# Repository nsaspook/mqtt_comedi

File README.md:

C programs for interfacing a Comedi DAQ board to MQTT using jSON data format

For bmc Q84 board firmware and hardware files use branch: opifixes

For bmc Linux control for Orange Pi use branch: opifixes

For bmc Linux control for Rasperry Pi use branch: fixes64

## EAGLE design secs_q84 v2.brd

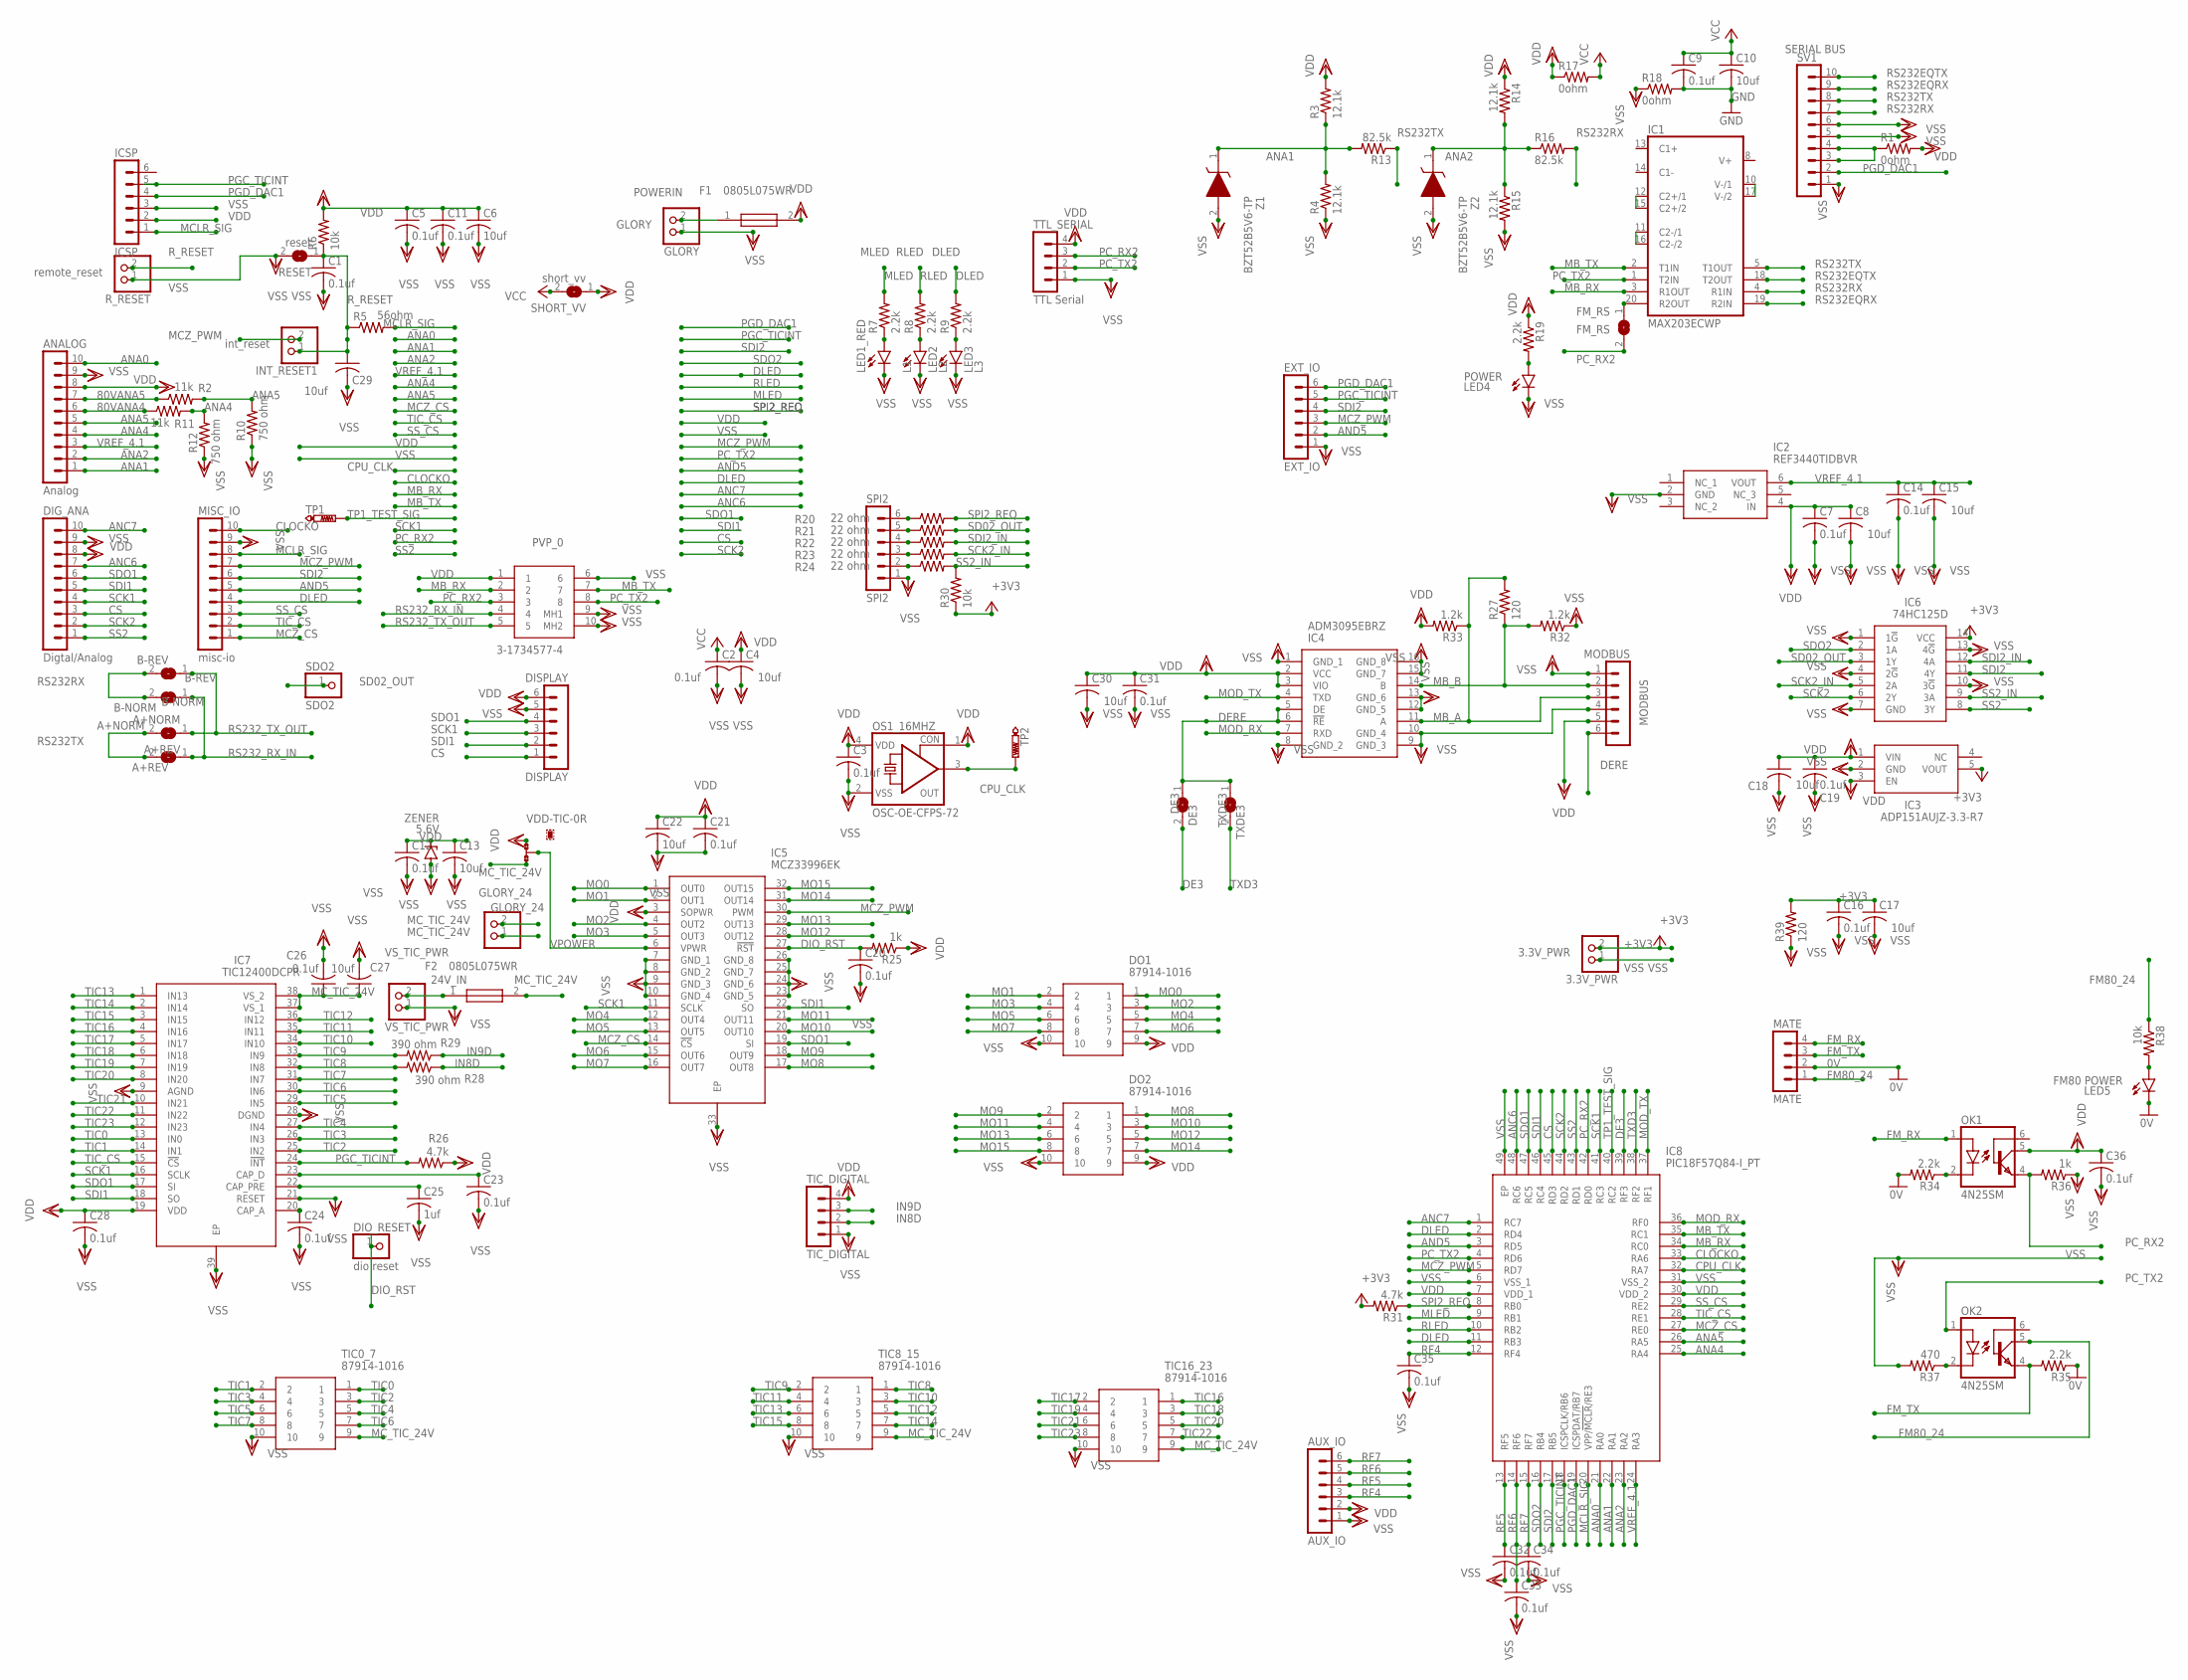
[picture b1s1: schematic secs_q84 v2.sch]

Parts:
3.3V_PWR: 3.3V_PWR; 1X02
A+NORM: A+NORM; SJ
A+REV: A+REV; SJ
ANALOG: Analog; MA10-1
AUX_IO: AUX_IO; MA06-1
B-NORM: B-NORM; SJ
B-REV: B-REV; SJ
C1, C2, C3, C5, C7, C9, C11, C12, C14, C16, C19, C20, C21, C23, C24, C26, C28, C31: 0.1uf; C0805
C4, C6, C8, C10, C13, C15, C17, C18, C22, C27, C29, C30: 10uf; C0805
C25: 1uf; C0805
C32, C33, C34, C35, C36: 0.1uf; C0603
DE3: DE3; SJ
DIG_ANA: Digtal/Analog; MA10-1
DIO_RESET: dio reset; 1X01
DISPLAY: DISPLAY; MA06-1
DO1, DO2: 87914-1016; 879141016
EXT_IO: EXT_IO; MA06-1
F1, F2: 0805L075WR; FUSC2114X125N
FM_RS: FM_RS; SJ
GLORY: GLORY; 1X02
GLORY_24: GLORY_24; 1X02
IC1: MAX203ECWP; SO20L
IC2: REF3440TIDBVR; SOT95P280X145-6N
IC3: ADP151AUJZ-3.3-R7; SOT95P280X100-5N
IC4: ADM3095EBRZ; SOIC127P600X175-16N
IC5: MCZ33996EK; SOP65P1030X265-33N
IC6: 74HC125D; SOIC127P600X175-14N
IC7: TIC12400DCPR; SOP50P640X120-39N
IC8: PIC18F57Q84-I_PT; QFP50P900X900X120-49N
ICSP: ICSP; MA06-1
INT_RESET1: int_reset; 1X02
LED1_RED: L1; CHIPLED_0805
LED2: L2; CHIPLED_0805
LED3: L3; CHIPLED_0805
LED4: POWER; CHIP-LED0603
LED5: FM80 POWER; CHIP-LED0603
MATE: MATE; MA04-1
MISC_IO: misc-io; MA10-1
MODBUS: MODBUS; MA06-1
OK1, OK2: 4N25SM; DIL6-SMD
OS1_16MHZ: OSC-OE-CFPS-72; 7.2X5.2-4-PAD
PVP_0: 3-1734577-4; 317345774
R1, R17, R18: 0ohm; R0805
R2, R11: 11k; M1206
R3, R4, R14, R15: 12.1k; R0805
R5: 56ohm; R0805
R6, R30, R38: 10k; R0805
R7, R8, R9, R19, R34, R35: 2.2k; R0805
R10, R12: 750 ohm; M1206
R13, R16: 82.5k; R0805
R20, R21, R22, R23, R24: 22 ohm; R0805
R25, R36: 1k; R0805
R26, R31: 4.7k; R0805
R27, R39: 120; R0805
R28, R29: 390 ohm; R0805
R32, R33: 1.2k; R0805
R37: 470; R0805
RESET: reset; SJ
R_RESET: remote_reset; 1X02
SDO2: SDO2; 1X01
SHORT_VV: short_vv; SJ
SPI2: SPI2; MA06-1
SV1: SERIAL BUS; MA10-1
TIC0_7, TIC8_15, TIC16_23: 87914-1016; 879141016
TIC_DIGITAL: TIC_DIGITAL; MA04-1
TP1, TP2: PTR1PAD1-13; P1-13
TTL_SERIAL: TTL Serial; MA04-1
TXDE3: TXDE3; SJ
VDD-TIC: 0R-JUMPA; A0R-JMP
VS_TIC_PWR: VS_TIC_PWR; 1X02
Z1, Z2: BZT52B5V6-TP; SOD3716X135N
ZENER: 5.6V; SMB

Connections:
0V: LED5.C, MATE.2, R34.2, R35.1
24V_IN: F2.1, VS_TIC_PWR.2
80VANA4: ANALOG.6, R11.1
80VANA5: ANALOG.7, R2.1
+3V3: 3.3V_PWR.2, C16.1, C17.1, IC3.5 (VOUT), IC6.14 (VCC), R30.1, R31.2, R39.2
ANA0: ANALOG.10, IC8.21 (RA0)
ANA1: ANALOG.1, IC8.22 (RA1), R3.1, R4.2, R13.2, Z1.1 (K)
ANA2: ANALOG.2, IC8.23 (RA2), R14.2, R15.1, R16.1, Z2.1 (K)
ANA4: ANALOG.4, IC8.25 (RA4), R11.2, R12.2
ANA5: ANALOG.5, IC8.26 (RA5), R2.2, R10.2
ANC6: DIG_ANA.7, IC8.48 (RC6)
ANC7: DIG_ANA.10, IC8.1 (RC7)
AND5: EXT_IO.2, IC8.3 (RD5), MISC_IO.5
CLOCKO: IC8.33 (RA6), MISC_IO.10
CPU_CLK: IC8.32 (RA7), OS1_16MHZ.3 (OUT), TP2.TP
CS: DIG_ANA.3, DISPLAY.1, IC8.45 (RD3)
DE3: DE3.2, IC8.39 (RF3)
DERE: DE3.1, IC4.5 (DE), IC4.6 (!RE), MODBUS.6, TXDE3.1
DIO_RST: C20.1, DIO_RESET.1, IC5.27 (!RST), R25.2
DLED: IC8.2 (RD4), IC8.11 (RB3), MISC_IO.4, R9.2
DPOWER: R1.1, SV1.3, SV1.4
FM80_24: MATE.1, OK2.5 (COL), R38.1
FM_RX: MATE.4, OK1.1 (A)
FM_TX: MATE.3, OK2.4 (EMI), R35.2
GND: C9.2, C10.2, IC1.6 (GND), IC1.9 (GND), R18.2
IN8D: R28.1, TIC_DIGITAL.2
IN9D: R29.1, TIC_DIGITAL.3
MB_A: IC4.11 (A), MODBUS.3, R27.2, R33.1
MB_B: IC4.14 (B), MODBUS.2, R27.1, R32.2
MB_RX: IC1.3 (R1OUT), IC8.34 (RC0), PVP_0.2
MB_TX: IC1.2 (T1IN), IC8.35 (RC1), PVP_0.7
MCLR_SIG: IC8.20 (VPP/!MCLR!/RE3), ICSP.1, MISC_IO.8, R5.2
MCZ_CS: IC5.14 (!CS), IC8.27 (RE0), MISC_IO.1
MCZ_PWM: EXT_IO.3, IC5.30 (PWM), IC8.5 (RD7), INT_RESET1.2, MISC_IO.7
MC_TIC_24V: C26.1, C27.1, F2.2, GLORY_24.1, GLORY_24.2, IC7.37 (VS_1), IC7.38 (VS_2), TIC0_7.9, TIC8_15.9, TIC16_23.9, VDD-TIC.3
MLED: IC8.9 (RB1), R7.2
MO0: DO1.1, IC5.1 (OUT0)
MO1: DO1.2, IC5.2 (OUT1)
MO2: DO1.3, IC5.4 (OUT2)
MO3: DO1.4, IC5.5 (OUT3)
MO4: DO1.5, IC5.12 (OUT4)
MO5: DO1.6, IC5.13 (OUT5)
MO6: DO1.7, IC5.15 (OUT6)
MO7: DO1.8, IC5.16 (OUT7)
MO8: DO2.1, IC5.17 (OUT8)
MO9: DO2.2, IC5.18 (OUT9)
MO10: DO2.3, IC5.20 (OUT10)
MO11: DO2.4, IC5.21 (OUT11)
MO12: DO2.5, IC5.28 (OUT12)
MO13: DO2.6, IC5.29 (OUT13)
MO14: DO2.7, IC5.31 (OUT14)
MO15: DO2.8, IC5.32 (OUT15)
MOD_RX: IC4.7 (RXD), IC8.36 (RF0)
MOD_TX: IC4.4 (TXD), IC8.37 (RF1)
unnamed: IC1.10 (V-/1), IC1.17 (V-/2)
unnamed: IC1.12 (C2+/1), IC1.15 (C2+/2)
unnamed: LED4.A, R19.2
unnamed: LED1_RED.A, R7.1
unnamed: LED2.A, R8.1
unnamed: LED3.A, R9.1
unnamed: IC1.11 (C2-/1), IC1.16 (C2-/2)
unnamed: R20.1, SPI2.6
unnamed: R21.1, SPI2.5
unnamed: R22.1, SPI2.4
unnamed: R23.1, SPI2.3
unnamed: R24.1, SPI2.2
unnamed: FM_RS.1, IC1.20 (R2OUT)
unnamed: OK1.2 (C), R34.1
unnamed: LED5.A, R38.2
unnamed: OK2.2 (C), R37.1
unnamed: C23.1, IC7.23 (CAP_D)
unnamed: C25.1, IC7.22 (CAP_PRE)
unnamed: C24.1, IC7.20 (CAP_A)
PC_RX2: FM_RS.2, IC8.42 (RD0), OK1.4 (EMI), PVP_0.3, R36.2, TTL_SERIAL.3
PC_TX2: IC1.1 (T2IN), IC8.4 (RD6), OK2.1 (A), PVP_0.8, TTL_SERIAL.2
PGC_TICINT: EXT_IO.5, IC7.24 (!INT), IC8.18 (ICSPCLK/RB6), ICSP.5, R26.2
PGD_DAC1: EXT_IO.6, IC8.19 (ICSPDAT/RB7), ICSP.4, SV1.2
POWERIN: F1.1, GLORY.2
RF4: AUX_IO.3, C35.1, IC8.12 (RF4)
RF5: AUX_IO.4, C32.1, IC8.13 (RF5)
RF6: AUX_IO.5, C33.1, IC8.14 (RF6)
RF7: AUX_IO.6, C34.1, IC8.15 (RF7)
RLED: IC8.10 (RB2), R8.2
RS232EQRX: IC1.19 (R2IN), SV1.9
RS232EQTX: IC1.18 (T2OUT), SV1.10
RS232RX: B-NORM.2, B-REV.2, IC1.4 (R1IN), R16.2, SV1.7
RS232TX: A+NORM.2, A+REV.2, IC1.5 (T1OUT), R13.1, SV1.8
RS232_RX_IN: A+REV.1, B-NORM.1, PVP_0.4
RS232_TX_OUT: A+NORM.1, B-REV.1, PVP_0.5
R_RESET: C1.1, C29.1, INT_RESET1.1, R5.1, R6.1, RESET.1, R_RESET.2
SCK1: DIG_ANA.4, DISPLAY.3, IC5.11 (SCLK), IC7.16 (SCLK), IC8.41 (RC3)
SCK2: DIG_ANA.2, IC6.6 (2Y), IC8.44 (RD2)
SCK2_IN: IC6.5 (2A), R23.2
SD02_OUT: IC6.3 (1Y), R21.2, SDO2.1
SDI1: DIG_ANA.5, DISPLAY.2, IC5.22 (SO), IC7.18 (SO), IC8.46 (RC4)
SDI2: EXT_IO.4, IC6.11 (4Y), IC8.17 (RB5), MISC_IO.6
SDI2_IN: IC6.12 (4A), R22.2
SDO1: DIG_ANA.6, DISPLAY.4, IC5.19 (SI), IC7.17 (SI), IC8.47 (RC5)
SDO2: IC6.2 (1A), IC8.16 (RB4)
SPI2_REQ: IC8.8 (RB0), R20.2, R31.1
SS2: DIG_ANA.1, IC6.8 (3Y), IC8.43 (RD1)
SS2_IN: IC6.9 (3A), R24.2, R30.2
SS_CS: IC8.29 (RE2), MISC_IO.3
TIC0: IC7.13 (IN0), TIC0_7.1
TIC1: IC7.14 (IN1), TIC0_7.2
TIC2: IC7.25 (IN2), TIC0_7.3
TIC3: IC7.26 (IN3), TIC0_7.4
TIC4: IC7.27 (IN4), TIC0_7.5
TIC5: IC7.29 (IN5), TIC0_7.6
TIC6: IC7.30 (IN6), TIC0_7.7
TIC7: IC7.31 (IN7), TIC0_7.8
TIC8: IC7.32 (IN8), R28.2, TIC8_15.1
TIC9: IC7.33 (IN9), R29.2, TIC8_15.2
TIC10: IC7.34 (IN10), TIC8_15.3
TIC11: IC7.35 (IN11), TIC8_15.4
TIC12: IC7.36 (IN12), TIC8_15.5
TIC13: IC7.1 (IN13), TIC8_15.6
TIC14: IC7.2 (IN14), TIC8_15.7
TIC15: IC7.3 (IN15), TIC8_15.8
TIC16: IC7.4 (IN16), TIC16_23.1
TIC17: IC7.5 (IN17), TIC16_23.2
TIC18: IC7.6 (IN18), TIC16_23.3
TIC19: IC7.7 (IN19), TIC16_23.4
TIC20: IC7.8 (IN20), TIC16_23.5
TIC21: IC7.10 (IN21), TIC16_23.6
TIC22: IC7.11 (IN22), TIC16_23.7
TIC23: IC7.12 (IN23), TIC16_23.8
TIC_CS: IC7.15 (!CS), IC8.28 (RE1), MISC_IO.2
TP1_TEST_SIG: IC8.40 (RC2), TP1.TP
TXD3: IC8.38 (RF2), TXDE3.2
VCC: C2.1, C9.1, C10.1, IC1.7 (VCC), R17.2, SHORT_VV.2
VDD: ANALOG.8, AUX_IO.2, C3.1, C4.1, C5.1, C6.1, C7.1, C8.1, C11.1, C12.1, C13.1, C18.1, C19.1, C21.1, C22.1, C28.1, C30.1, C31.1, C36.1, DIG_ANA.8, DISPLAY.6, DO1.9, DO2.9, F1.2, IC2.4 (IN), IC3.1 (VIN), IC3.3 (EN), IC4.2 (VCC), IC4.3 (VIO), IC5.3 (SOPWR), IC7.19 (VDD), IC8.7 (VDD_1), IC8.30 (VDD_2), ICSP.2, MODBUS.5, OK1.5 (COL), OS1_16MHZ.1 (CON), OS1_16MHZ.4 (VDD), PVP_0.1, R1.2, R3.2, R6.2, R14.1, R17.1, R19.1, R25.1, R26.1, R33.2, SHORT_VV.1, TIC_DIGITAL.4, TTL_SERIAL.4, VDD-TIC.1, ZENER.C
VPOWER: IC5.6 (VPWR), VDD-TIC.2
VREF_4.1: ANALOG.3, C14.1, C15.1, IC2.6 (VOUT), IC8.24 (RA3)
VSS: 3.3V_PWR.1, ANALOG.9, AUX_IO.1, C1.2, C2.2, C3.2, C4.2, C5.2, C6.2, C7.2, C8.2, C11.2, C12.2, C13.2, C14.2, C15.2, C16.2, C17.2, C18.2, C19.2, C20.2, C21.2, C22.2, C23.2, C24.2, C25.2, C26.2, C27.2, C28.2, C29.2, C30.2, C31.2, C32.2, C33.2, C34.2, C35.2, C36.2, DIG_ANA.9, DISPLAY.5, DO1.10, DO2.10, EXT_IO.1, GLORY.1, IC2.2 (GND), IC3.2 (GND), IC4.1 (GND_1), IC4.8 (GND_2), IC4.9 (GND_3), IC4.10 (GND_4), IC4.12 (GND_5), IC4.13 (GND_6), IC4.15 (GND_7), IC4.16 (GND_8), IC5.7 (GND_1), IC5.8 (GND_2), IC5.9 (GND_3), IC5.10 (GND_4), IC5.23 (GND_5), IC5.24 (GND_6), IC5.25 (GND_7), IC5.26 (GND_8), IC5.33 (EP), IC6.1 (1!G), IC6.4 (2!G), IC6.7 (GND), IC6.10 (3!G), IC6.13 (4!G), IC7.9 (AGND), IC7.21 (RESET), IC7.28 (DGND), IC7.39 (EP), IC8.6 (VSS_1), IC8.31 (VSS_2), IC8.49 (EP), ICSP.3, LED1_RED.C, LED2.C, LED3.C, LED4.C, MISC_IO.9, MODBUS.1, MODBUS.4, OS1_16MHZ.2 (VSS), PVP_0.6, PVP_0.9 (MH1), PVP_0.10 (MH2), R4.1, R10.1, R12.1, R15.2, R18.1, R32.1, R36.1, R37.2, R39.1, RESET.2, R_RESET.1, SPI2.1, SV1.1, SV1.5, SV1.6, TIC0_7.10, TIC8_15.10, TIC16_23.10, TIC_DIGITAL.1, TTL_SERIAL.1, VS_TIC_PWR.1, Z1.2 (A), Z2.2 (A), ZENER.A

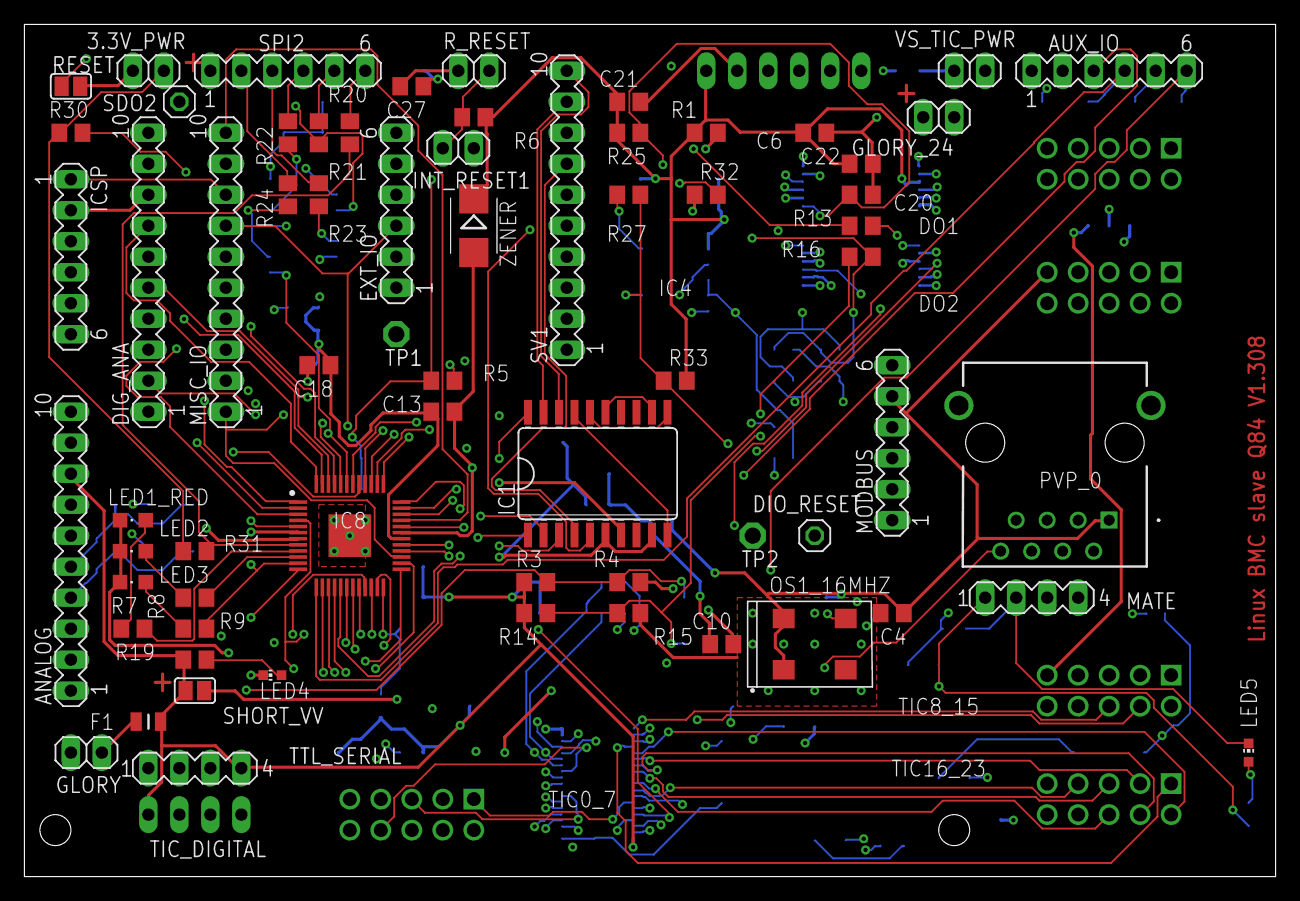
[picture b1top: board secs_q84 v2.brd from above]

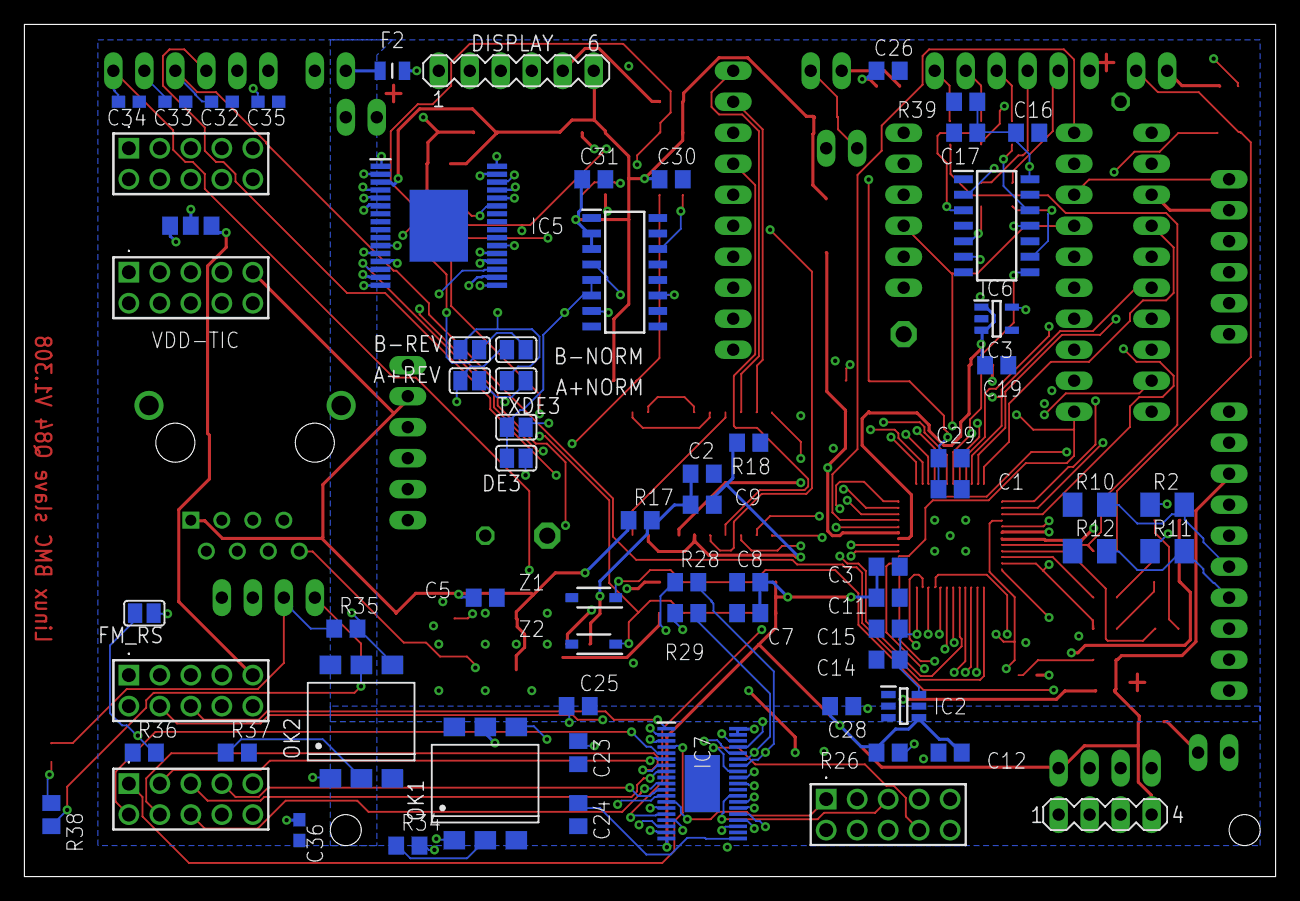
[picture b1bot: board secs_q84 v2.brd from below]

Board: 4 copper layers, 102.5 x 69.8 mm, 135 parts (68 on the bottom side), 135 nets.

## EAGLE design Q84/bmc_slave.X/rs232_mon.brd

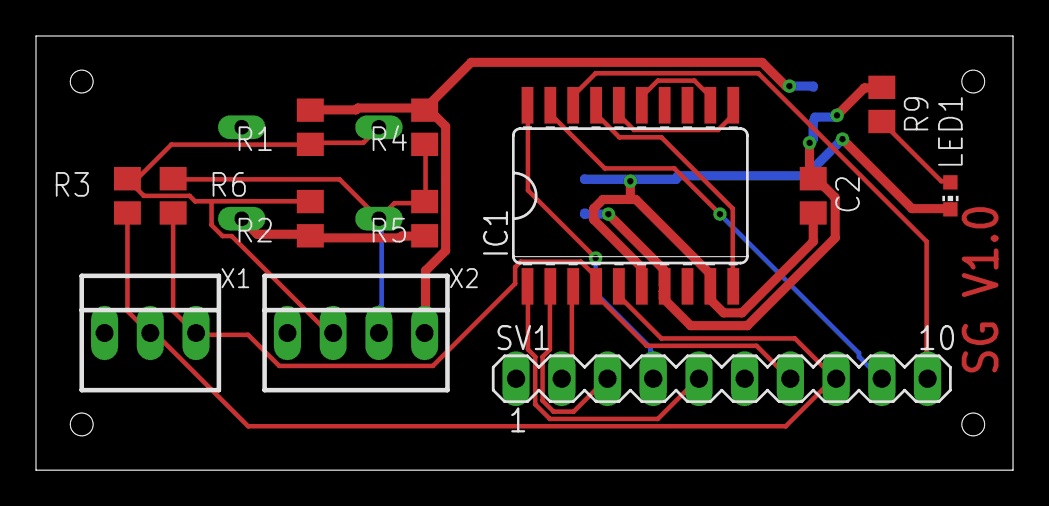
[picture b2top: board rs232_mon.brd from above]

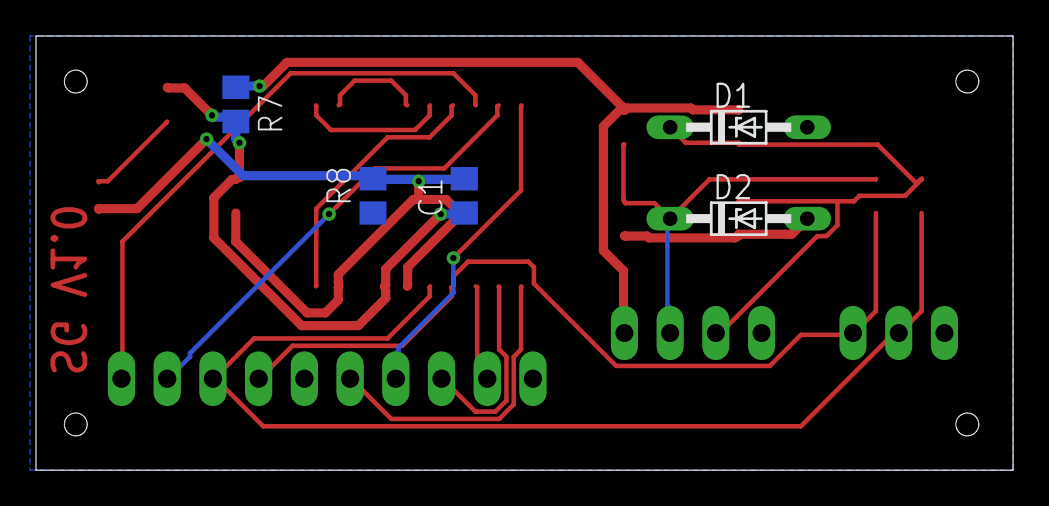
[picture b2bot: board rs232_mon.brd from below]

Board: 2 copper layers, 54.3 x 24.1 mm, 18 parts (5 on the bottom side), 18 nets.

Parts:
C1: 0.1uf; C0805
C2: 10uf; C0805
D1, D2: 5.6V; DO34Z7
IC1: MAX203ECWP; SO20L
LED1: POWER; CHIP-LED0603
R1, R2, R4, R5: 12.1k; R0805
R3, R6: 86.6k; R0805
R7, R8: 0ohm; R0805
R9: 1k; R0805
SV1: SERIAL BUS; MA10-1
X1: RS232 LINES; 22-23-2031
X2: ADC POWER; 22-23-2041

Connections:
EQRX: IC1.20, SV1.4
EQTX: IC1.1, SV1.5
GND: C1.2, C2.2, IC1.6, IC1.9, LED1.C, R8.2
MCURX: IC1.3, SV1.2
MCUTX: IC1.2, SV1.3
unnamed: D1.C, R1.1, R2.2, R3.2, X2.2
unnamed: D2.C, R4.2, R5.1, R6.1, X2.3
unnamed: LED1.A, R9.2
unnamed: IC1.10, IC1.17
unnamed: IC1.11, IC1.16
unnamed: IC1.12, IC1.15
RS232EQRX: IC1.19, SV1.9
RS232EQTX: IC1.18, SV1.10
RS232RX: IC1.4, R6.2, SV1.7, X1.3
RS232TX: IC1.5, R3.1, SV1.8, X1.2
VCC: C1.1, C2.1, IC1.7, R7.2, R9.1
VDD: R1.2, R4.1, R7.1, X2.4
VSS: D1.A, D2.A, R2.1, R5.2, R8.1, SV1.1, SV1.6, X1.1, X2.1

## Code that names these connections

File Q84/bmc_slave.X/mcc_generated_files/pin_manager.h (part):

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// get/set channel_ANA0 aliases
#define channel_ANA0_TRIS                 TRISAbits.TRISA0
#define channel_ANA0_LAT                  LATAbits.LATA0
#define channel_ANA0_PORT                 PORTAbits.RA0
#define channel_ANA0_WPU                  WPUAbits.WPUA0
#define channel_ANA0_OD                   ODCONAbits.ODCA0
#define channel_ANA0_ANS                  ANSELAbits.ANSELA0
#define channel_ANA0_SetHigh()            do { LATAbits.LATA0 = 1; } while(0)
#define channel_ANA0_SetLow()             do { LATAbits.LATA0 = 0; } while(0)
#define channel_ANA0_Toggle()             do { LATAbits.LATA0 = ~LATAbits.LATA0; } while(0)
#define channel_ANA0_GetValue()           PORTAbits.RA0
#define channel_ANA0_SetDigitalInput()    do { TRISAbits.TRISA0 = 1; } while(0)
#define channel_ANA0_SetDigitalOutput()   do { TRISAbits.TRISA0 = 0; } while(0)
#define channel_ANA0_SetPullup()          do { WPUAbits.WPUA0 = 1; } while(0)
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// get/set channel_ANA1 aliases
#define channel_ANA1_TRIS                 TRISAbits.TRISA1
#define channel_ANA1_LAT                  LATAbits.LATA1
#define channel_ANA1_PORT                 PORTAbits.RA1
#define channel_ANA1_WPU                  WPUAbits.WPUA1
#define channel_ANA1_OD                   ODCONAbits.ODCA1
#define channel_ANA1_ANS                  ANSELAbits.ANSELA1
#define channel_ANA1_SetHigh()            do { LATAbits.LATA1 = 1; } while(0)
#define channel_ANA1_SetLow()             do { LATAbits.LATA1 = 0; } while(0)
#define channel_ANA1_Toggle()             do { LATAbits.LATA1 = ~LATAbits.LATA1; } while(0)
#define channel_ANA1_GetValue()           PORTAbits.RA1
#define channel_ANA1_SetDigitalInput()    do { TRISAbits.TRISA1 = 1; } while(0)
#define channel_ANA1_SetDigitalOutput()   do { TRISAbits.TRISA1 = 0; } while(0)
#define channel_ANA1_SetPullup()          do { WPUAbits.WPUA1 = 1; } while(0)
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// get/set channel_ANA2 aliases
#define channel_ANA2_TRIS                 TRISAbits.TRISA2
#define channel_ANA2_LAT                  LATAbits.LATA2
#define channel_ANA2_PORT                 PORTAbits.RA2
#define channel_ANA2_WPU                  WPUAbits.WPUA2
#define channel_ANA2_OD                   ODCONAbits.ODCA2
#define channel_ANA2_ANS                  ANSELAbits.ANSELA2
#define channel_ANA2_SetHigh()            do { LATAbits.LATA2 = 1; } while(0)
#define channel_ANA2_SetLow()             do { LATAbits.LATA2 = 0; } while(0)
#define channel_ANA2_Toggle()             do { LATAbits.LATA2 = ~LATAbits.LATA2; } while(0)
#define channel_ANA2_GetValue()           PORTAbits.RA2
#define channel_ANA2_SetDigitalInput()    do { TRISAbits.TRISA2 = 1; } while(0)
#define channel_ANA2_SetDigitalOutput()   do { TRISAbits.TRISA2 = 0; } while(0)
#define channel_ANA2_SetPullup()          do { WPUAbits.WPUA2 = 1; } while(0)
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#define RA3_SetHigh()            do { LATAbits.LATA3 = 1; } while(0)
#define RA3_SetLow()             do { LATAbits.LATA3 = 0; } while(0)
#define RA3_Toggle()             do { LATAbits.LATA3 = ~LATAbits.LATA3; } while(0)
#define RA3_GetValue()              PORTAbits.RA3
#define RA3_SetDigitalInput()    do { TRISAbits.TRISA3 = 1; } while(0)
#define RA3_SetDigitalOutput()   do { TRISAbits.TRISA3 = 0; } while(0)
#define RA3_SetPullup()             do { WPUAbits.WPUA3 = 1; } while(0)
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// get/set channel_ANA4 aliases
#define channel_ANA4_TRIS                 TRISAbits.TRISA4
#define channel_ANA4_LAT                  LATAbits.LATA4
#define channel_ANA4_PORT                 PORTAbits.RA4
#define channel_ANA4_WPU                  WPUAbits.WPUA4
#define channel_ANA4_OD                   ODCONAbits.ODCA4
#define channel_ANA4_ANS                  ANSELAbits.ANSELA4
#define channel_ANA4_SetHigh()            do { LATAbits.LATA4 = 1; } while(0)
#define channel_ANA4_SetLow()             do { LATAbits.LATA4 = 0; } while(0)
#define channel_ANA4_Toggle()             do { LATAbits.LATA4 = ~LATAbits.LATA4; } while(0)
#define channel_ANA4_GetValue()           PORTAbits.RA4
#define channel_ANA4_SetDigitalInput()    do { TRISAbits.TRISA4 = 1; } while(0)
#define channel_ANA4_SetDigitalOutput()   do { TRISAbits.TRISA4 = 0; } while(0)
#define channel_ANA4_SetPullup()          do { WPUAbits.WPUA4 = 1; } while(0)
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// get/set channel_ANA5 aliases
#define channel_ANA5_TRIS                 TRISAbits.TRISA5
#define channel_ANA5_LAT                  LATAbits.LATA5
#define channel_ANA5_PORT                 PORTAbits.RA5
#define channel_ANA5_WPU                  WPUAbits.WPUA5
#define channel_ANA5_OD                   ODCONAbits.ODCA5
#define channel_ANA5_ANS                  ANSELAbits.ANSELA5
#define channel_ANA5_SetHigh()            do { LATAbits.LATA5 = 1; } while(0)
#define channel_ANA5_SetLow()             do { LATAbits.LATA5 = 0; } while(0)
#define channel_ANA5_Toggle()             do { LATAbits.LATA5 = ~LATAbits.LATA5; } while(0)
#define channel_ANA5_GetValue()           PORTAbits.RA5
#define channel_ANA5_SetDigitalInput()    do { TRISAbits.TRISA5 = 1; } while(0)
#define channel_ANA5_SetDigitalOutput()   do { TRISAbits.TRISA5 = 0; } while(0)
#define channel_ANA5_SetPullup()          do { WPUAbits.WPUA5 = 1; } while(0)
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// get/set SPI2_REQ aliases
#define SPI2_REQ_TRIS                 TRISBbits.TRISB0
#define SPI2_REQ_LAT                  LATBbits.LATB0
#define SPI2_REQ_PORT                 PORTBbits.RB0
#define SPI2_REQ_WPU                  WPUBbits.WPUB0
#define SPI2_REQ_OD                   ODCONBbits.ODCB0
#define SPI2_REQ_ANS                  ANSELBbits.ANSELB0
#define SPI2_REQ_SetHigh()            do { LATBbits.LATB0 = 1; } while(0)
#define SPI2_REQ_SetLow()             do { LATBbits.LATB0 = 0; } while(0)
#define SPI2_REQ_Toggle()             do { LATBbits.LATB0 = ~LATBbits.LATB0; } while(0)
#define SPI2_REQ_GetValue()           PORTBbits.RB0
#define SPI2_REQ_SetDigitalInput()    do { TRISBbits.TRISB0 = 1; } while(0)
#define SPI2_REQ_SetDigitalOutput()   do { TRISBbits.TRISB0 = 0; } while(0)
#define SPI2_REQ_SetPullup()          do { WPUBbits.WPUB0 = 1; } while(0)
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// get/set MLED aliases
#define MLED_TRIS                 TRISBbits.TRISB1
#define MLED_LAT                  LATBbits.LATB1
#define MLED_PORT                 PORTBbits.RB1
#define MLED_WPU                  WPUBbits.WPUB1
#define MLED_OD                   ODCONBbits.ODCB1
#define MLED_ANS                  ANSELBbits.ANSELB1
#define MLED_SetHigh()            do { LATBbits.LATB1 = 1; } while(0)
#define MLED_SetLow()             do { LATBbits.LATB1 = 0; } while(0)
#define MLED_Toggle()             do { LATBbits.LATB1 = ~LATBbits.LATB1; } while(0)
#define MLED_GetValue()           PORTBbits.RB1
#define MLED_SetDigitalInput()    do { TRISBbits.TRISB1 = 1; } while(0)
#define MLED_SetDigitalOutput()   do { TRISBbits.TRISB1 = 0; } while(0)
#define MLED_SetPullup()          do { WPUBbits.WPUB1 = 1; } while(0)
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// get/set RLED aliases
#define RLED_TRIS                 TRISBbits.TRISB2
#define RLED_LAT                  LATBbits.LATB2
#define RLED_PORT                 PORTBbits.RB2
#define RLED_WPU                  WPUBbits.WPUB2
#define RLED_OD                   ODCONBbits.ODCB2
#define RLED_ANS                  ANSELBbits.ANSELB2
#define RLED_SetHigh()            do { LATBbits.LATB2 = 1; } while(0)
#define RLED_SetLow()             do { LATBbits.LATB2 = 0; } while(0)
#define RLED_Toggle()             do { LATBbits.LATB2 = ~LATBbits.LATB2; } while(0)
#define RLED_GetValue()           PORTBbits.RB2
#define RLED_SetDigitalInput()    do { TRISBbits.TRISB2 = 1; } while(0)
#define RLED_SetDigitalOutput()   do { TRISBbits.TRISB2 = 0; } while(0)
#define RLED_SetPullup()          do { WPUBbits.WPUB2 = 1; } while(0)
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// get/set DLED aliases
#define DLED_TRIS                 TRISBbits.TRISB3
#define DLED_LAT                  LATBbits.LATB3
#define DLED_PORT                 PORTBbits.RB3
#define DLED_WPU                  WPUBbits.WPUB3
#define DLED_OD                   ODCONBbits.ODCB3
#define DLED_ANS                  ANSELBbits.ANSELB3
#define DLED_SetHigh()            do { LATBbits.LATB3 = 1; } while(0)
#define DLED_SetLow()             do { LATBbits.LATB3 = 0; } while(0)
#define DLED_Toggle()             do { LATBbits.LATB3 = ~LATBbits.LATB3; } while(0)
#define DLED_GetValue()           PORTBbits.RB3
#define DLED_SetDigitalInput()    do { TRISBbits.TRISB3 = 1; } while(0)
#define DLED_SetDigitalOutput()   do { TRISBbits.TRISB3 = 0; } while(0)
#define DLED_SetPullup()          do { WPUBbits.WPUB3 = 1; } while(0)
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#define RB4_SetHigh()            do { LATBbits.LATB4 = 1; } while(0)
#define RB4_SetLow()             do { LATBbits.LATB4 = 0; } while(0)
#define RB4_Toggle()             do { LATBbits.LATB4 = ~LATBbits.LATB4; } while(0)
#define RB4_GetValue()              PORTBbits.RB4
#define RB4_SetDigitalInput()    do { TRISBbits.TRISB4 = 1; } while(0)
#define RB4_SetDigitalOutput()   do { TRISBbits.TRISB4 = 0; } while(0)
#define RB4_SetPullup()             do { WPUBbits.WPUB4 = 1; } while(0)
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#define RB5_SetHigh()            do { LATBbits.LATB5 = 1; } while(0)
#define RB5_SetLow()             do { LATBbits.LATB5 = 0; } while(0)
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
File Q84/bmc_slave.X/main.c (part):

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 */

/*
 * UART3 MODBUS serial comms, MODBUS header:: A-PIN 3 , B-PIN 2 , DERE-PIN 6, VSS-PIN 1 and 4, VDD-PIN 5, interrupts, 9600 bps MOD_RX/MOD_TX
 *
 * UART2 FMx0 serial comms 9-bits async OPTO isolated MATE header:: FM_RX-PIN 4, FM_TX-PIN 3, FM_0V-PIN 2, FM_24V-PIN 1,
 * UART2 TTL serial HEADER:: RX-PIN 3, TX-PIN 2, VSS-PIN 1, VDD-PIN 4, SV1 serial header:: TX-PIN 10, RX-PIN 9, VSS-PIN 6, interrupts, polled. 9600 bps PC_RX/PC_TX
 *
 * UART1 general serial comms, PVP JACK connector:: RS232 TX-PIN 5, RX-PIN 4 VSS-PIN 6,  SV1 serial header::, TX-PIN 8, RX-PIN 7, VSS-PIN 6,
 * UART1 PVP JACK connector:: TTL TX-PIN 5, RX-PIN 7 VSS-PIN 6, interrupts, 115200 bps MB_RX/MB_TX
 *
 * Energy Meter Model
 * AUX IO pin 4, RF4,RF5,RF7 EMETER_CONF_TYPE, EMETER_CONF, EMETER_CONF_TYPE1
 * jumper RF5 to low/common for WEM30 meters
 * jumper RF4 and RF5 to low/common for PZEM meters
 * jumper RF7 to low/common for custom meters
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#pragma config FCMENS = ON      // Fail-Safe Clock Monitor -Secondary XTAL Enable bit (FSCM timer will set FSCMS bit and OSFIF interrupt on Secondary XTAL failure)

// CONFIG3
#pragma config MCLRE = EXTMCLR  // MCLR Enable bit (If LVP = 0, MCLR pin is MCLR; If LVP = 1, RE3 pin function is MCLR )
#pragma config PWRTS = PWRT_OFF // Power-up timer selection bits (PWRT is disabled)
#pragma config MVECEN = ON      // Multi-vector enable bit (Multi-vector enabled, Vector table used for interrupts)
#pragma config IVT1WAY = OFF     // IVTLOCK bit One-way set enable bit (IVTLOCKED bit can be cleared and set only once)
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#pragma config WRTAPP = OFF     // Application Block write protection bit (Application Block not write protected)

// CONFIG9
#pragma config BOOTPINSEL = RC5 // CRC on boot output pin selection (CRC on boot output pin is RC5)
#pragma config BPEN = OFF       // CRC on boot output pin enable bit (CRC on boot output pin disabled)
#pragma config ODCON = OFF      // CRC on boot output pin open drain bit (Pin drives both high-going and low-going signals)

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
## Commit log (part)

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2025-05-21 up board pictures
2025-06-19 add frame
2025-06-22 10 second resets
2025-07-03 fix analog kernel threads
2025-07-06 PCB updates:wq
2025-07-08 update before cleaning
2025-07-09 up clean up driver
2025-07-17 update to 9 byte packets for all commands via SPI
2025-07-22 BETA Version
2025-07-22 cleanup
2025-07-22 update degub logging, notes were off key
2025-07-23 add patches
2025-07-24 up AO thread speed
2025-07-29 uuse 57Q84
2025-07-30 up uuuppp# modified: secs_q84 v2.b#5
2025-08-01 57Q84 support
2025-08-04 add FM80 interface
2025-08-08 up for f47
2025-08-09 merger 47 version into 57 version
2025-08-10 serial data fixes
2025-08-12 up cleanup
2025-08-14 cal analog inputs
2025-08-16 up# modified: Q84/bmc_slave.X/nbproject/Makefile-genesis.properties
2025-08-16 update to modbus and fm80 drivers
2025-08-17 add new code for serial interfaces
2025-08-17 update doc
2025-08-18 cleanup of code smells
2025-08-18 updates for new functions and hardware
2025-08-27 MQTT code from the FM80 and EM540
2025-09-01 V0.35 cleanup
2025-09-07 use calib table values for HV calibration
2025-09-12 add calibration data to data stream
2025-09-12 use C11 for Opi BMC program source
2025-09-15 fix missing BMCBoard detection
2025-10-11 convert defines to const
2025-10-23 cleanups
2025-10-24 add config file code
2026-01-09 V1.0
2026-01-09 up diagram
2026-01-29 RPI changes to the bmc user application
2026-02-15 update bmc for the opi systems
2026-02-15 update to new bmc version
2026-02-16 cherry pic changes from rpibmc fixes branch
2026-03-05 uupp# modified: Q84/bmc_slave.X/dist/default/production/bmc_slave.X.production.elf
2026-03-12 SPI link fixes
2026-03-14 update energy displays
2026-03-19 up bmc fixes
2026-03-23 add PZEM-6L24 energy meter
2026-04-04 fix PZEM data and displays
2026-04-28 sync code
2026-05-18 update doxygen
2026-05-18 doxygen update
2026-05-22 add PZEM AC power data
2026-05-22 testing daq700 card data
2026-05-25 update ISR usage tracking
2026-06-03 ID not sane calibration values
2026-06-03 ID not sane values

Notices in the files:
Q84/bmc_slave.X/mcc_generated_files/pin_manager.h:
(c) 2018 Microchip Technology Inc. and its subsidiaries.
